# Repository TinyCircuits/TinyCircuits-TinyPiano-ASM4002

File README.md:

# TinyCircuits TinyPiano, ASM4002
# ASM4002 Rev2

These are the design files for the TinyCircuits TinyPiano ASM4002 Rev 2 PCB. This is a small open source piano with capacitive touch piano keys, an ATTiny processor and a coin cell battery for power

Format is in Cadsoft Eagle format - Eagle version 6.3 was used for the original design.

For more information on this, check out the product page at TinyCircuits.com: https://tinycircuits.com/tinypiano

## License

Design by TinyCircuits.
All design files are released under the Creative Commons Attribution Share-Alike 3.0 License, see the following link for details: http://creativecommons.org/licenses/by-sa/3.0

All text above must be included in any redistribution or derived design

This project uses designs and concepts developed as part of the Arduino project and the LilyPad project.  The TinyCircuits design files themselves (schematics, PCB and libraries) are not directly derived from these works' design files and have been created new, however the concepts and basic architecture behind the TinyDuino and TinyLily products are derived and we thank the hard work of the organizations below for their contributions to open-source hardware:
  
Original Arduino Uno Design by Team Arduino

LilyPad Arduino Design by Leah Buechley and Sparkfun Electronics

Please support the open-source hardware community

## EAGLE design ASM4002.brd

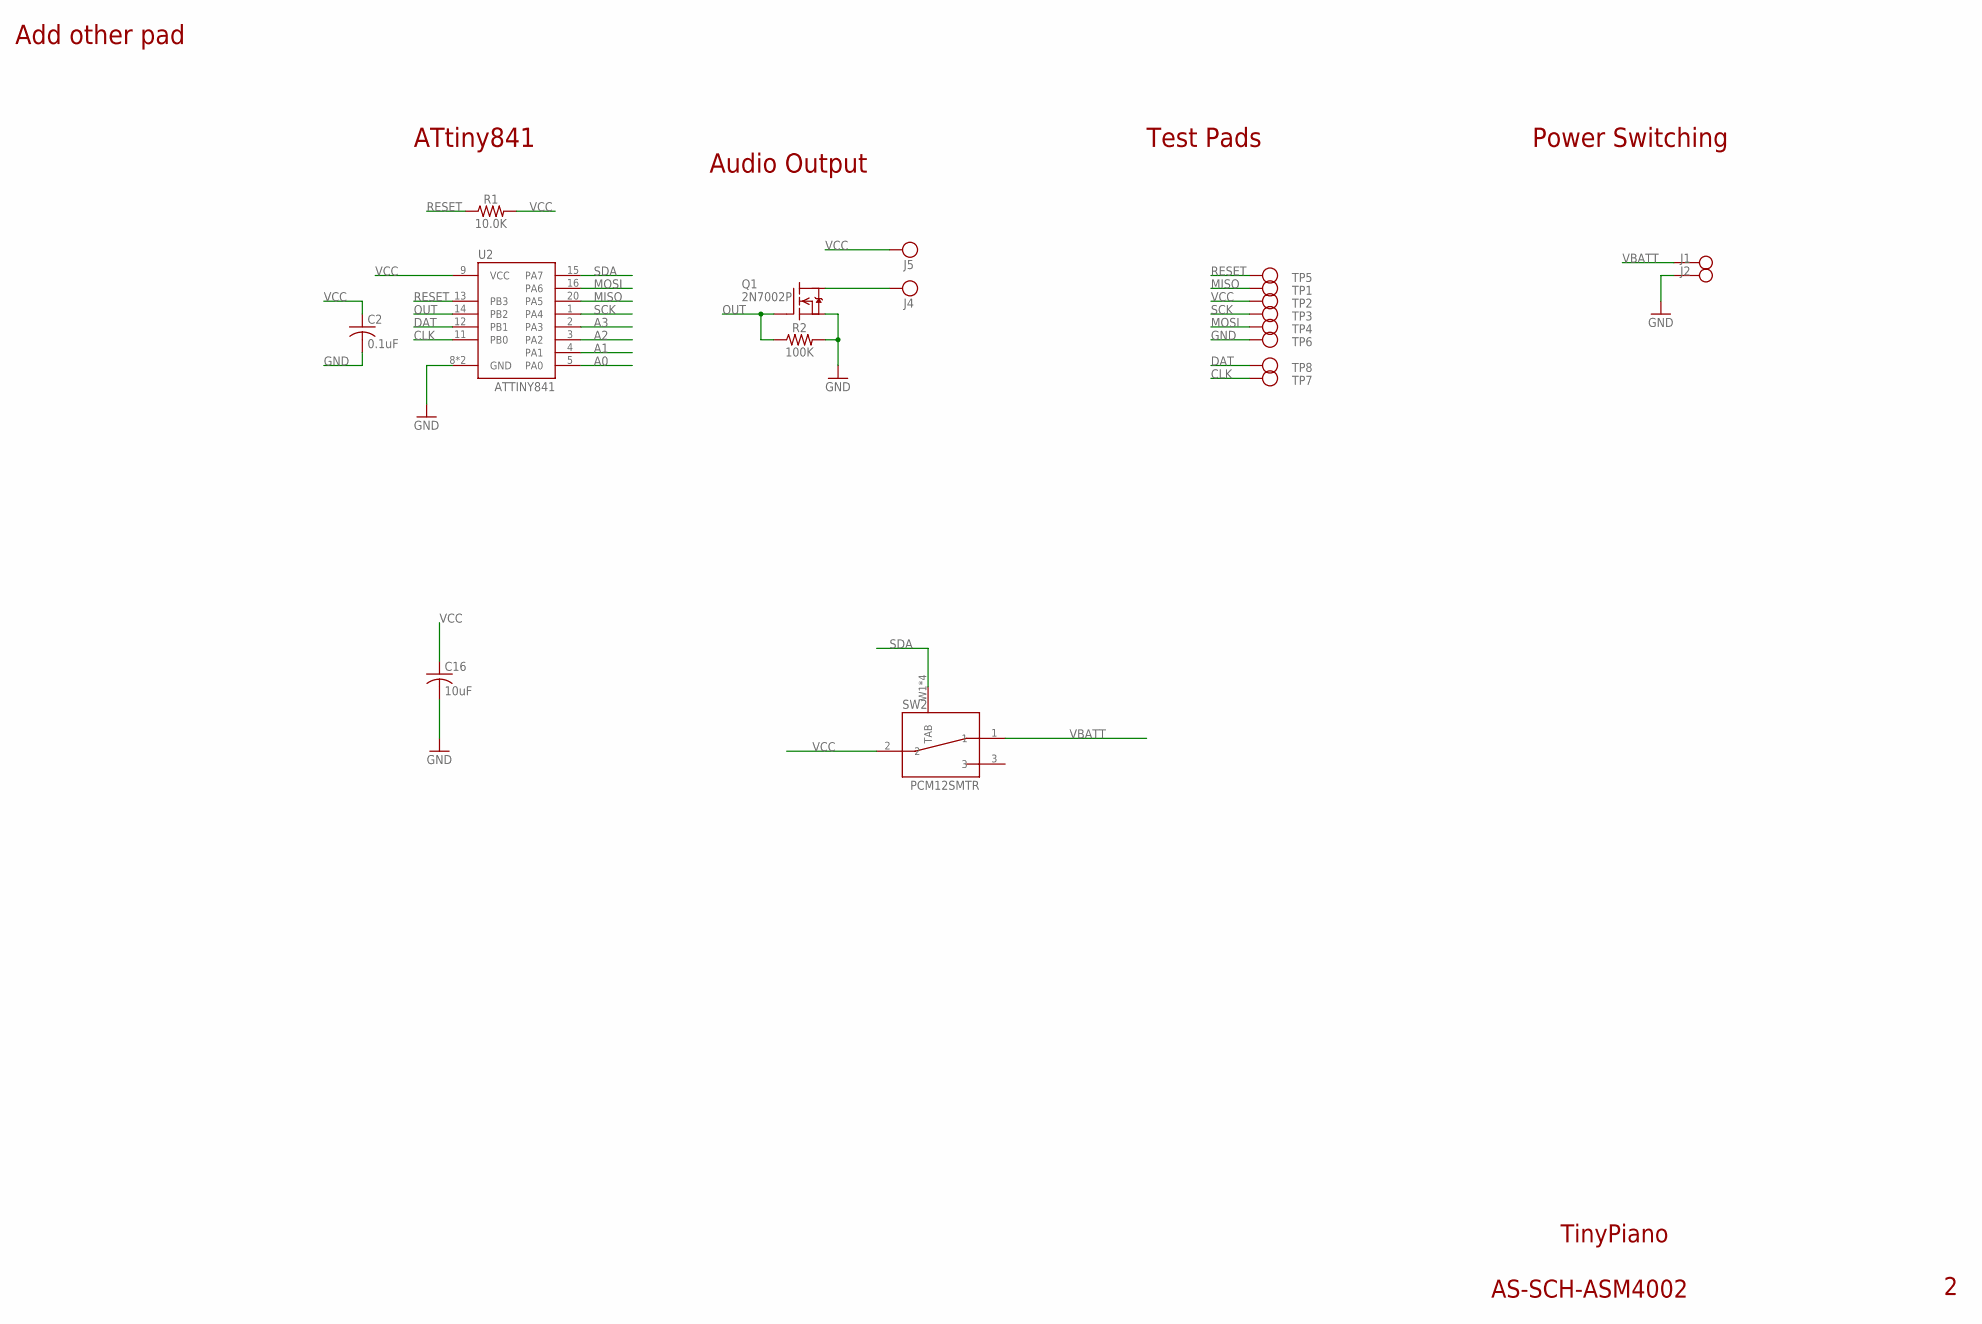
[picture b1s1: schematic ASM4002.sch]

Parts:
C2: 0.1uF; C0402
C16: 10uF; C0603; PARTNO AS-ITM-00002
J1: PIN_1X.1"; 1.4MM_TH
J2: 1.4MM_TH
J4, J5: PIN_1X.1"1; 1X.1"_2
Q1: 2N7002P; SOT23A
R1: 10.0K; 0402
R2: 100K; 0402
SW2: PCM12SMTR
TP1, TP2, TP3, TP4, TP5, TP6, TP7, TP8: TEST_POINT; TEST_POINT_1MM
U2: ATTINY841; VQFN-20

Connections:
A0: U2.5 (PA0)
A1: U2.4 (PA1)
A2: U2.3 (PA2)
A3: U2.2 (PA3)
CLK: TP7.P$1, U2.11 (PB0)
DAT: TP8.P$1, U2.12 (PB1)
GND: C2.2, C16.2, J2.P$1, Q1.E (S), R2.2, TP6.P$1, U2.8 (GND), U2.PAD (GND)
MISO: TP1.P$1, U2.20 (PA5)
MOSI: TP4.P$1, U2.16 (PA6)
unnamed: J4.1, Q1.C (D)
OUT: Q1.B (G), R2.1, U2.14 (PB2)
RESET: R1.1, TP5.P$1, U2.13 (PB3)
SCK: TP3.P$1, U2.1 (PA4)
SDA: SW2.W1 (TAB), SW2.W2 (TAB), SW2.W3 (TAB), SW2.W4 (TAB), U2.15 (PA7)
VBATT: J1.P$1, SW2.1
VCC: C2.1, C16.1, J5.1, R1.2, SW2.2, TP2.P$1, U2.9 (VCC)

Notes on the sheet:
TinyPiano
AS-SCH-ASM4002
Test Pads
ATtiny841
Power Switching
Audio Output
Add other pad

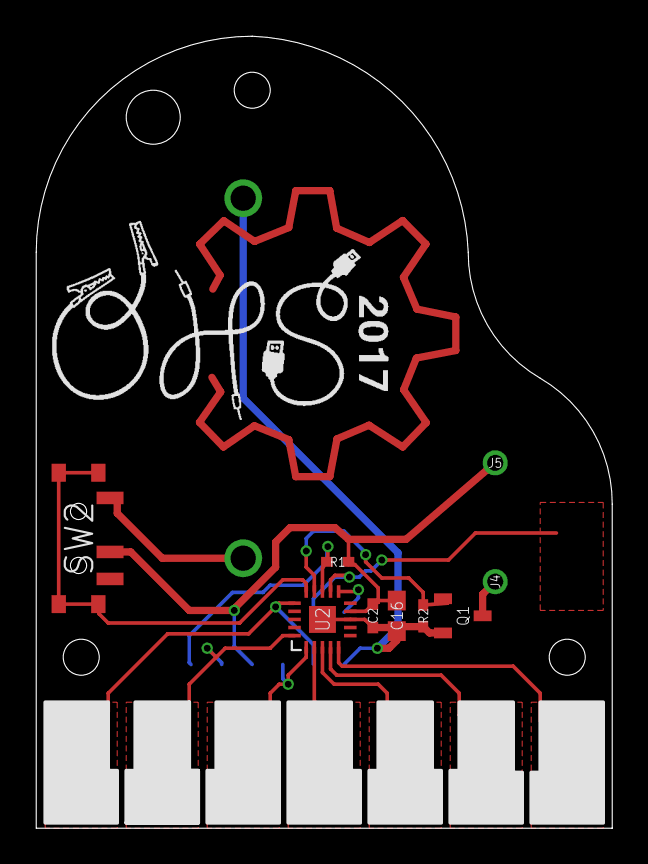
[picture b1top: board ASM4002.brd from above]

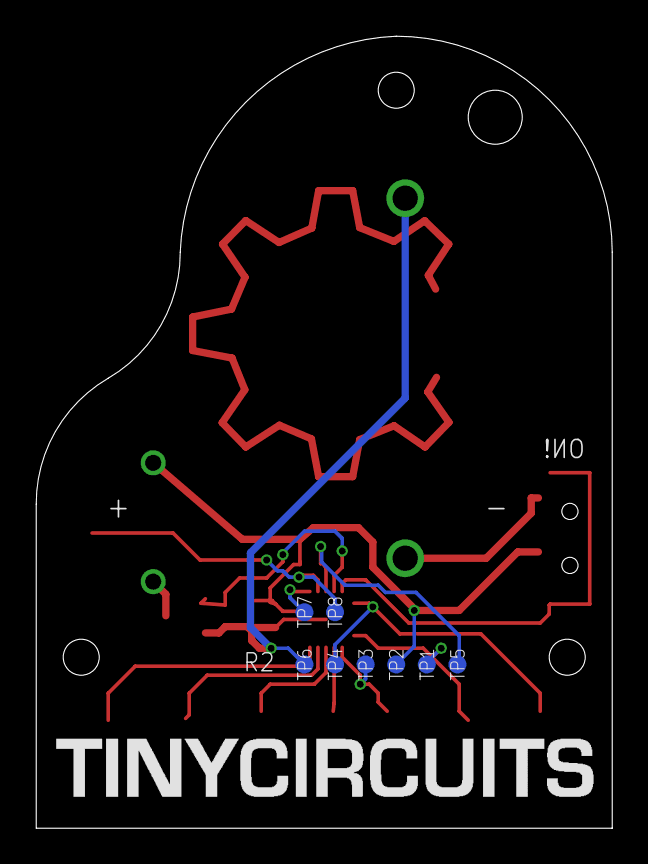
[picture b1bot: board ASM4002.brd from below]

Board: 2 copper layers, 32.0 x 44.0 mm, 20 parts (8 on the bottom side), 12 nets.

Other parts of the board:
U$1: DOCFIELD-TINYCIRCUITS-PCB

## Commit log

2017-10-03 :space_invader: Added .gitattributes & .gitignore files
2019-08-01 pics
2019-08-02 TPiano
2019-08-02 schematic
